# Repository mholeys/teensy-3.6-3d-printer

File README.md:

# Teensy 3.6 3D printer

KiCad board of my 3D printer

Uses a Teensy 3.6 - https://www.pjrc.com/store/teensy36.html
This requires most pins (including pins on the bottom of the teensy, as such I have left space for a row of wires to be soldered from the bottom of the teensy to the board.
This board was designed to replace a Anet A8 board so not all 3D printer features have been planned or taken into account.

Disclaimer:
- I am not a electrical engineer or certified in anyway for work with electronics, I am happy to take the risk myself but if you use this design you take all responsability, for any damage and you accept this.

Problems:
- After having the boards produced, I noticed that I have made a mistake with the holes for the custom boards such as the the rear pin breakout, and the TMC2130 driver holes. This has not been a problem for me as I have some smaller round hole pin headers, which fit perfectly, but you may have to redesign or modify this board in order to use something different.
- After using the board for a while, I have noticed I have also undersized the traces! (BAD, same problem as the original Anet A8 baord). This can be fixed by adding additional cabling between the GND input and the stepper motors, and importantly the transistors for the hot ends. This may make this board dangerous to use, and another reason not to use this board AS IS. 

Uses:
- https://github.com/XenGi/teensy_library
- https://github.com/XenGi/teensy.pretty

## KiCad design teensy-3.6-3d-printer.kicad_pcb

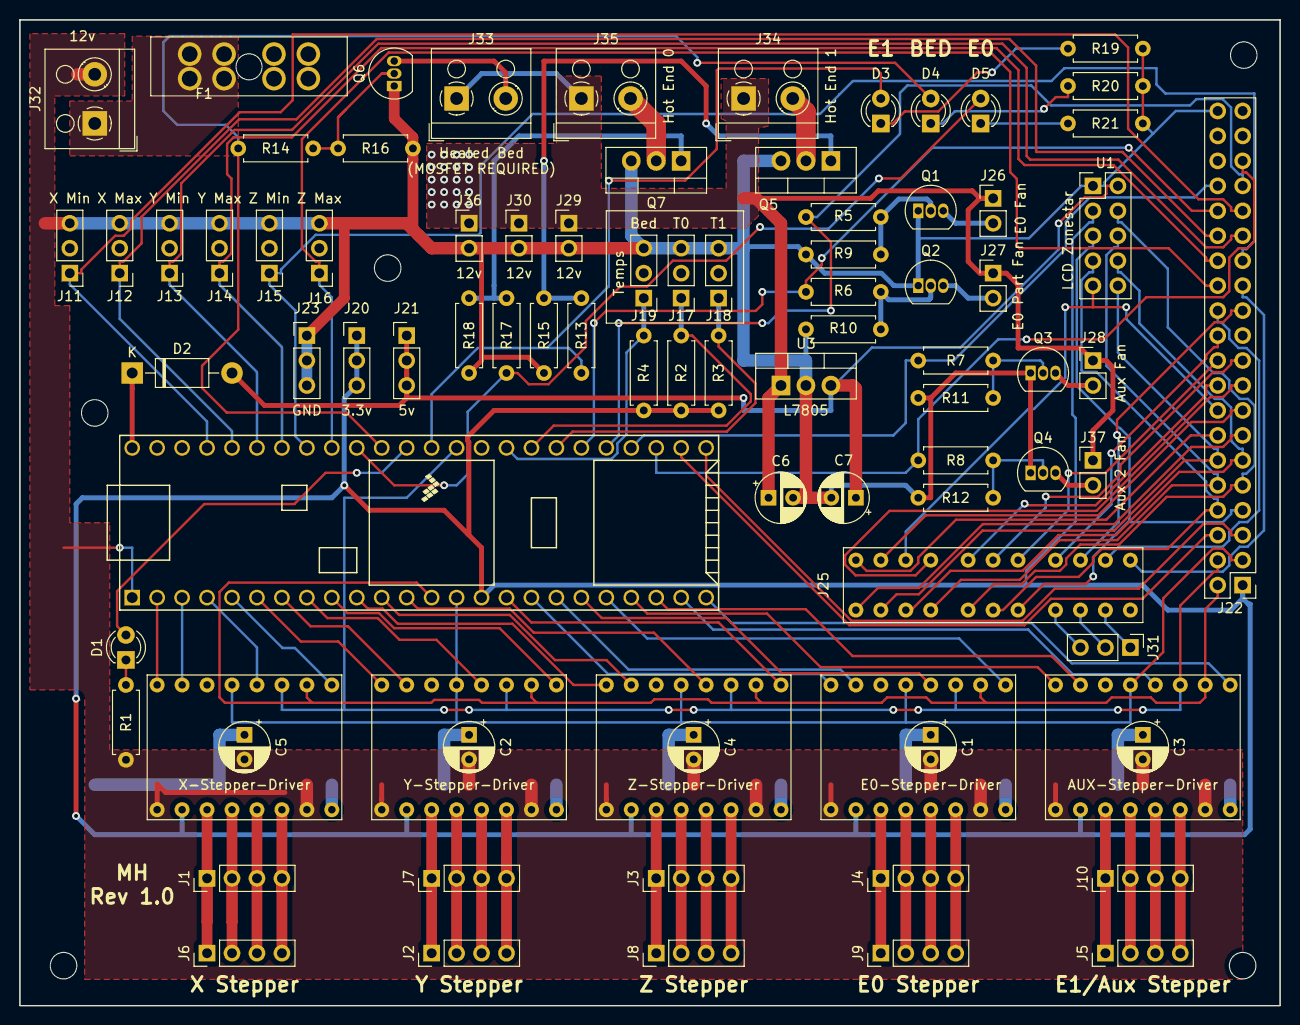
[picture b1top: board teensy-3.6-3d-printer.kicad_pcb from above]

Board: 2 copper layers, 128.3 x 100.3 mm, 85 parts (0 on the bottom side), 107 nets.

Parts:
AUX-Stepper-Driver: TMC2130-Board; tmc2130-driver
C1, C2, C3, C4, C5: 100uf; CP_Radial_D5.0mm_P2.50mm
C6: 0.33uf; CP_Radial_D5.0mm_P2.50mm
C7: 0.1uf; CP_Radial_D5.0mm_P2.50mm
D1, D3, D4, D5: LED; LED_D3.0mm
D2: DIODE_SCHOTTKY_15V_1A; D_DO-41_SOD81_P10.16mm_Horizontal
E0-Stepper-Driver: TMC2130-Board; tmc2130-driver
F1: Fuse; Pudenz-30a-PCB-ATO-Fuseholder
J1, J6: X_STEPPER; PinHeader_1x04_P2.54mm_Vertical
J2, J7: Y_STEPPER; PinHeader_1x04_P2.54mm_Vertical
J3, J8: Z_STEPPER; PinHeader_1x04_P2.54mm_Vertical
J4, J9: E0_STEPPER; PinHeader_1x04_P2.54mm_Vertical
J5, J10: AUX_STEPPER; PinHeader_1x04_P2.54mm_Vertical
J11: X-Min-Limit; PinHeader_1x03_P2.54mm_Vertical
J12: X-Max-Limit; PinHeader_1x03_P2.54mm_Vertical
J13: Y-Min-Limit; PinHeader_1x03_P2.54mm_Vertical
J14: Y-Max-Limit; PinHeader_1x03_P2.54mm_Vertical
J15: Z-Min-Limit; PinHeader_1x03_P2.54mm_Vertical
J16: Z-Max-Limit; PinHeader_1x03_P2.54mm_Vertical
J17: Temp0; PinHeader_1x03_P2.54mm_Vertical
J18: Temp1; PinHeader_1x03_P2.54mm_Vertical
J19: Bed-Temp; PinHeader_1x03_P2.54mm_Vertical
J20: 3.3V; PinHeader_1x03_P2.54mm_Vertical
J21: 5V; PinHeader_1x03_P2.54mm_Vertical
J22: Conn_02x20_Counter_Clockwise; PinHeader_2x20_P2.54mm_Vertical
J23: GND; PinHeader_1x03_P2.54mm_Vertical
J25: teensy_back_pins; teensy-back
J26: Extruder 0 Fan; PinHeader_1x02_P2.54mm_Vertical
J27: Extruder 0 Part Fan; PinHeader_1x02_P2.54mm_Vertical
J28: Aux Fan; PinHeader_1x02_P2.54mm_Vertical
J29, J30, J36: 12V; PinHeader_1x02_P2.54mm_Vertical
J31: Debug; PinHeader_1x03_P2.54mm_Vertical
J32: Printer Power IN; TerminalBlock_RND_205-00001_1x02_P5.00mm_Horizontal
J33: Heated Bed; TerminalBlock_RND_205-00001_1x02_P5.00mm_Horizontal
J34: Hot End 1; TerminalBlock_RND_205-00001_1x02_P5.00mm_Horizontal
J35: Hot End 0; TerminalBlock_RND_205-00001_1x02_P5.00mm_Horizontal
J37: Aux 2 Fan; PinHeader_1x02_P2.54mm_Vertical
Q1, Q2, Q3, Q4, Q6: PN2222A; TO-92_Inline
Q5, Q7: IRLZ44N; TO-220-3_Vertical
R1, R14, R19, R20, R21: R; R_Axial_DIN0207_L6.3mm_D2.5mm_P7.62mm_Horizontal
R2, R3, R4: 4.7K; R_Axial_DIN0207_L6.3mm_D2.5mm_P7.62mm_Horizontal
R5, R6, R7, R8, R13, R17: 1K; R_Axial_DIN0207_L6.3mm_D2.5mm_P7.62mm_Horizontal
R9, R10, R11, R12, R15, R16, R18: 100K; R_Axial_DIN0207_L6.3mm_D2.5mm_P7.62mm_Horizontal
U1: Zonestar-LCD2004; PinHeader_2x05_P2.54mm_Vertical
U2: Teensy3.6; Teensy35_36
U3: L7805; TO-220-3_Vertical
X-Stepper-Driver: TMC2130-Board; tmc2130-driver
Y-Stepper-Driver: TMC2130-Board; tmc2130-driver
Z-Stepper-Driver: TMC2130-Board; tmc2130-driver

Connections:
+3V3: AUX-Stepper-Driver.3, E0-Stepper-Driver.3, J20.1, J20.2, J20.3, J22.1, R2.1, R3.1, R4.1, U1.3, U2.15, X-Stepper-Driver.3, Y-Stepper-Driver.3, Z-Stepper-Driver.3
+5V: C7.1, D2.2, J21.1, J21.2, J21.3, U1.2, U3.3
+12V: AUX-Stepper-Driver.15, C1.1, C2.1, C3.1, C4.1, C5.1, C6.1, E0-Stepper-Driver.15, F1.1, J26.1, J27.1, J28.1, J29.1, J30.1, J33.1, J34.1, J35.1, J36.1, J37.1, U3.1, X-Stepper-Driver.15, Y-Stepper-Driver.15, Z-Stepper-Driver.15
AUX2_FAN: J22.35, R8.2, U2.32
AUX2_FAN_12V: J37.2, Q4.3
AUX_CS: AUX-Stepper-Driver.10, U2.23
AUX_DIR: AUX-Stepper-Driver.2, U2.21
AUX_ENABLE: AUX-Stepper-Driver.16, U2.24
AUX_FAN: J22.34, R7.2, U2.33
AUX_FAN_12V: J28.2, Q3.3
AUX_RX: J22.5, U2.30
AUX_STEP: AUX-Stepper-Driver.4, U2.22
AUX_TX: J22.6, U2.31
BACK_46: J22.13, J25.46
BACK_47: J22.14, J25.47
BACK_48: J22.15, J25.48
BACK_50: J22.17, J25.50
BACK_51: J22.18, J25.51
BACK_52: J22.19, J25.52
BACK_53: J22.20, J25.53
BACK_54: J22.22, J25.54
BACK_55: J22.23, J25.55
BACK_56: J22.24, J25.56
BACK_57: J22.25, J25.57
BED_HEATER_12V: J33.2, Q6.3
E0_CS: E0-Stepper-Driver.10, U2.19
E0_DIR: E0-Stepper-Driver.2, U2.17
E0_ENABLE: E0-Stepper-Driver.16, U2.20
E0_FAN: J22.33, R5.2, U2.34
E0_FAN_12V: J26.2, Q1.3
E0_HEATER_12V: J35.2, Q7.2
E0_PART_FAN: J22.32, R6.2, U2.35
E0_PART_FAN_12V: J27.2, Q2.3
E0_STEP: E0-Stepper-Driver.4, U2.18
E1_HEATER_12V: J34.2, Q5.2
GND: AUX-Stepper-Driver.1, AUX-Stepper-Driver.13, C1.2, C2.2, C3.2, C4.2, C5.2, C6.2, C7.2, E0-Stepper-Driver.1, E0-Stepper-Driver.13, J11.3, J12.3, J13.3, J14.3, J15.3, J16.3, J17.3, J18.3, J19.3, J22.40, J23.1, J23.2, J23.3, J29.2, J30.2, J32.2, J36.2, Q1.1, Q2.1, Q3.1, Q4.1, Q5.3, Q6.1, Q7.3, R1.1, R9.1, R10.1, R11.1, R12.1, R15.2, R16.1, R18.2, R19.1, R20.1, R21.1, U1.1, U2.1, U3.2, X-Stepper-Driver.1, X-Stepper-Driver.13, Y-Stepper-Driver.1, Y-Stepper-Driver.13, Z-Stepper-Driver.1, Z-Stepper-Driver.13
HEATER_BED: D4.2, R14.2, U2.43
HEATER_E0: D5.2, R17.2, U2.44
HEATER_E1: D3.2, R13.2, U2.41
LCD_ADC_KEYPAD: J22.16, J25.49, U1.9
LCD_D4: J22.9, J25.42, U1.4
LCD_D5: J22.10, J25.43, U1.6
LCD_D6: J22.11, J25.44, U1.8
LCD_D7: J22.12, J25.45, U1.10
LCD_ENABLE: J22.8, J25.41, U1.7
LCD_RESET: J22.7, J25.40, U1.5
MISO: AUX-Stepper-Driver.8, E0-Stepper-Driver.8, J22.3, U2.14, X-Stepper-Driver.8, Y-Stepper-Driver.8, Z-Stepper-Driver.8
MOSI: AUX-Stepper-Driver.14, E0-Stepper-Driver.14, J22.2, U2.13, X-Stepper-Driver.14, Y-Stepper-Driver.14, Z-Stepper-Driver.14
unnamed: AUX-Stepper-Driver.5, J5.1, J10.1
unnamed: AUX-Stepper-Driver.7, J5.2, J10.2
unnamed: AUX-Stepper-Driver.9, J5.3, J10.3
unnamed: AUX-Stepper-Driver.11, J5.4, J10.4
unnamed: D1.1, R1.2
unnamed: D2.1, U2.53
unnamed: D3.1, R19.2
unnamed: D4.1, R20.2
unnamed: D5.1, R21.2
unnamed: E0-Stepper-Driver.5, J4.1, J9.1
unnamed: E0-Stepper-Driver.7, J4.2, J9.2
unnamed: E0-Stepper-Driver.9, J4.3, J9.3
unnamed: E0-Stepper-Driver.11, J4.4, J9.4
unnamed: F1.2, J32.1
unnamed: J1.1, J6.1, X-Stepper-Driver.5
unnamed: J1.2, J6.2, X-Stepper-Driver.7
unnamed: J1.3, J6.3, X-Stepper-Driver.9
unnamed: J1.4, J6.4, X-Stepper-Driver.11
unnamed: J2.1, J7.1, Y-Stepper-Driver.5
unnamed: J2.2, J7.2, Y-Stepper-Driver.7
unnamed: J2.3, J7.3, Y-Stepper-Driver.9
unnamed: J2.4, J7.4, Y-Stepper-Driver.11
unnamed: J3.1, J8.1, Z-Stepper-Driver.5
unnamed: J3.2, J8.2, Z-Stepper-Driver.7
unnamed: J3.3, J8.3, Z-Stepper-Driver.9
unnamed: J3.4, J8.4, Z-Stepper-Driver.11
unnamed: J25.DC, J31.2
unnamed: J25.DD, J31.3
unnamed: J25.DE, J31.1
unnamed: Q1.2, R5.1, R9.2
unnamed: Q2.2, R6.1, R10.2
unnamed: Q3.2, R7.1, R11.2
unnamed: Q4.2, R8.1, R12.2
unnamed: Q5.1, R13.1, R15.1
unnamed: Q6.2, R14.1, R16.2
unnamed: Q7.1, R17.1, R18.1
SCK: AUX-Stepper-Driver.12, E0-Stepper-Driver.12, J22.4, U2.40, X-Stepper-Driver.12, Y-Stepper-Driver.12, Z-Stepper-Driver.12
STATUS_LED: D1.2, U2.42
TEMP_BED: J19.1, R4.2, U2.38
TEMP_E0: J17.1, R2.2, U2.37
TEMP_E1: J18.1, R3.2, U2.36
X_CS: U2.4, X-Stepper-Driver.10
X_DIR: U2.2, X-Stepper-Driver.2
X_ENABLE: U2.5, X-Stepper-Driver.16
X_MAX: J12.1, J22.30, U2.49
X_MIN: J11.1, J22.31, U2.50
X_STEP: U2.3, X-Stepper-Driver.4
Y_CS: U2.8, Y-Stepper-Driver.10
Y_DIR: U2.6, Y-Stepper-Driver.2
Y_ENABLE: U2.9, Y-Stepper-Driver.16
Y_MAX: J14.1, J22.28, U2.47
Y_MIN: J13.1, J22.29, U2.48
Y_STEP: U2.7, Y-Stepper-Driver.4
Z_CS: U2.12, Z-Stepper-Driver.10
Z_DIR: U2.10, Z-Stepper-Driver.2
Z_ENABLE: U2.16, Z-Stepper-Driver.16
Z_MAX: J16.1, J22.26, U2.45
Z_MIN: J15.1, J22.27, U2.46
Z_STEP: U2.11, Z-Stepper-Driver.4

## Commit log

2019-12-10 Started teensy-3.6 schematic
2019-12-11 Teensy schematic finished
2020-01-08 Revision 1 finished
2020-06-12 Changed to new fuse holder, added filled zones
2021-08-05 Updated README.md - Warnings
